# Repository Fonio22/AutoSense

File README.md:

# AutoSense

AutoSense is an Edge-IoT vehicle monitoring project based on an ESP32-S3 OBD-II/CAN adapter, a React Native mobile app, Firebase services, and a LaTeX thesis document.

Repository: <https://github.com/Fonio22/AutoSense>

## What It Does

- Reads vehicle telemetry from OBD-II over CAN.
- Stores compact binary history locally on the ESP32-S3.
- Streams live telemetry to the mobile app through BLE.
- Exports unsynced binary logs from the ESP32-S3 to the app without deleting them from flash.
- Uploads historical log files to Firebase Storage and stores sync metadata in Firestore.
- Uses lightweight edge analysis with statistical baselines, Z-score, and Tiny Isolation Forest.
- Documents the project in the thesis under `Writting/main.tex`.

## Repository Layout

```text
OBD2-Firmware/       ESP32-S3 firmware, OBD-II service, BLE protocol, logger, anomaly analysis
app/                 Expo / React Native mobile app and Firebase rules
vehicle-profiles/    Vehicle profile definitions, including vw_passat_2016
kiCad/               PCB design and schematic files
outputs/             Processed datasets and exported analysis inputs
Writting/            LaTeX thesis source, figures, references, and compiled PDF
```

## Firmware

```bash
cd OBD2-Firmware
pio run
```

Main modules:

- `src/app.cpp`: boot sequence and main loop.
- `src/obd_service.cpp`: PID discovery, polling, and OBD-II decoding.
- `src/obd_binary_logger.*`: compact binary log storage and export.
- `src/obd_ble_protocol.*`: BLE commands, telemetry stream, and log sync.
- `src/anomaly_detector.*`: baseline, Z-score, Tiny Isolation Forest, and severity levels.

## Mobile App

```bash
cd app
npm install
npx tsc --noEmit
npm run lint
npm run ios
```

The app uses Expo Router, Firebase Auth, Firestore, Firebase Storage, SecureStore, BLE, and local file storage for downloaded OBD logs.

Profile resolver tests:

```bash
cd app
node --test functions/test/profile-resolver.test.mjs
```

## Thesis

```bash
cd Writting
latexmk -pdf -interaction=nonstopmode -file-line-error main.tex
```

Main files:

- `Writting/main.tex`: thesis source.
- `Writting/main.pdf`: generated thesis PDF.
- `Writting/Reference/references.bib`: bibliography.
- `Writting/Figures/`: diagrams, screenshots, test photos, and result charts.

## Validation Snapshot

The current thesis documents:

- Volkswagen Passat 2016 as the main real-vehicle validation profile.
- OBD-II simulator testing with a generic profile.
- A 60-day route-classified dataset with city, highway, and unknown segments.
- Functional tests for acquisition, BLE/USB communication, storage, visualization, and analysis.

## Safety Scope

AutoSense is designed as a read-only monitoring system. It does not erase diagnostic trouble codes, does not write to vehicle ECUs, and does not replace professional mechanical diagnosis.

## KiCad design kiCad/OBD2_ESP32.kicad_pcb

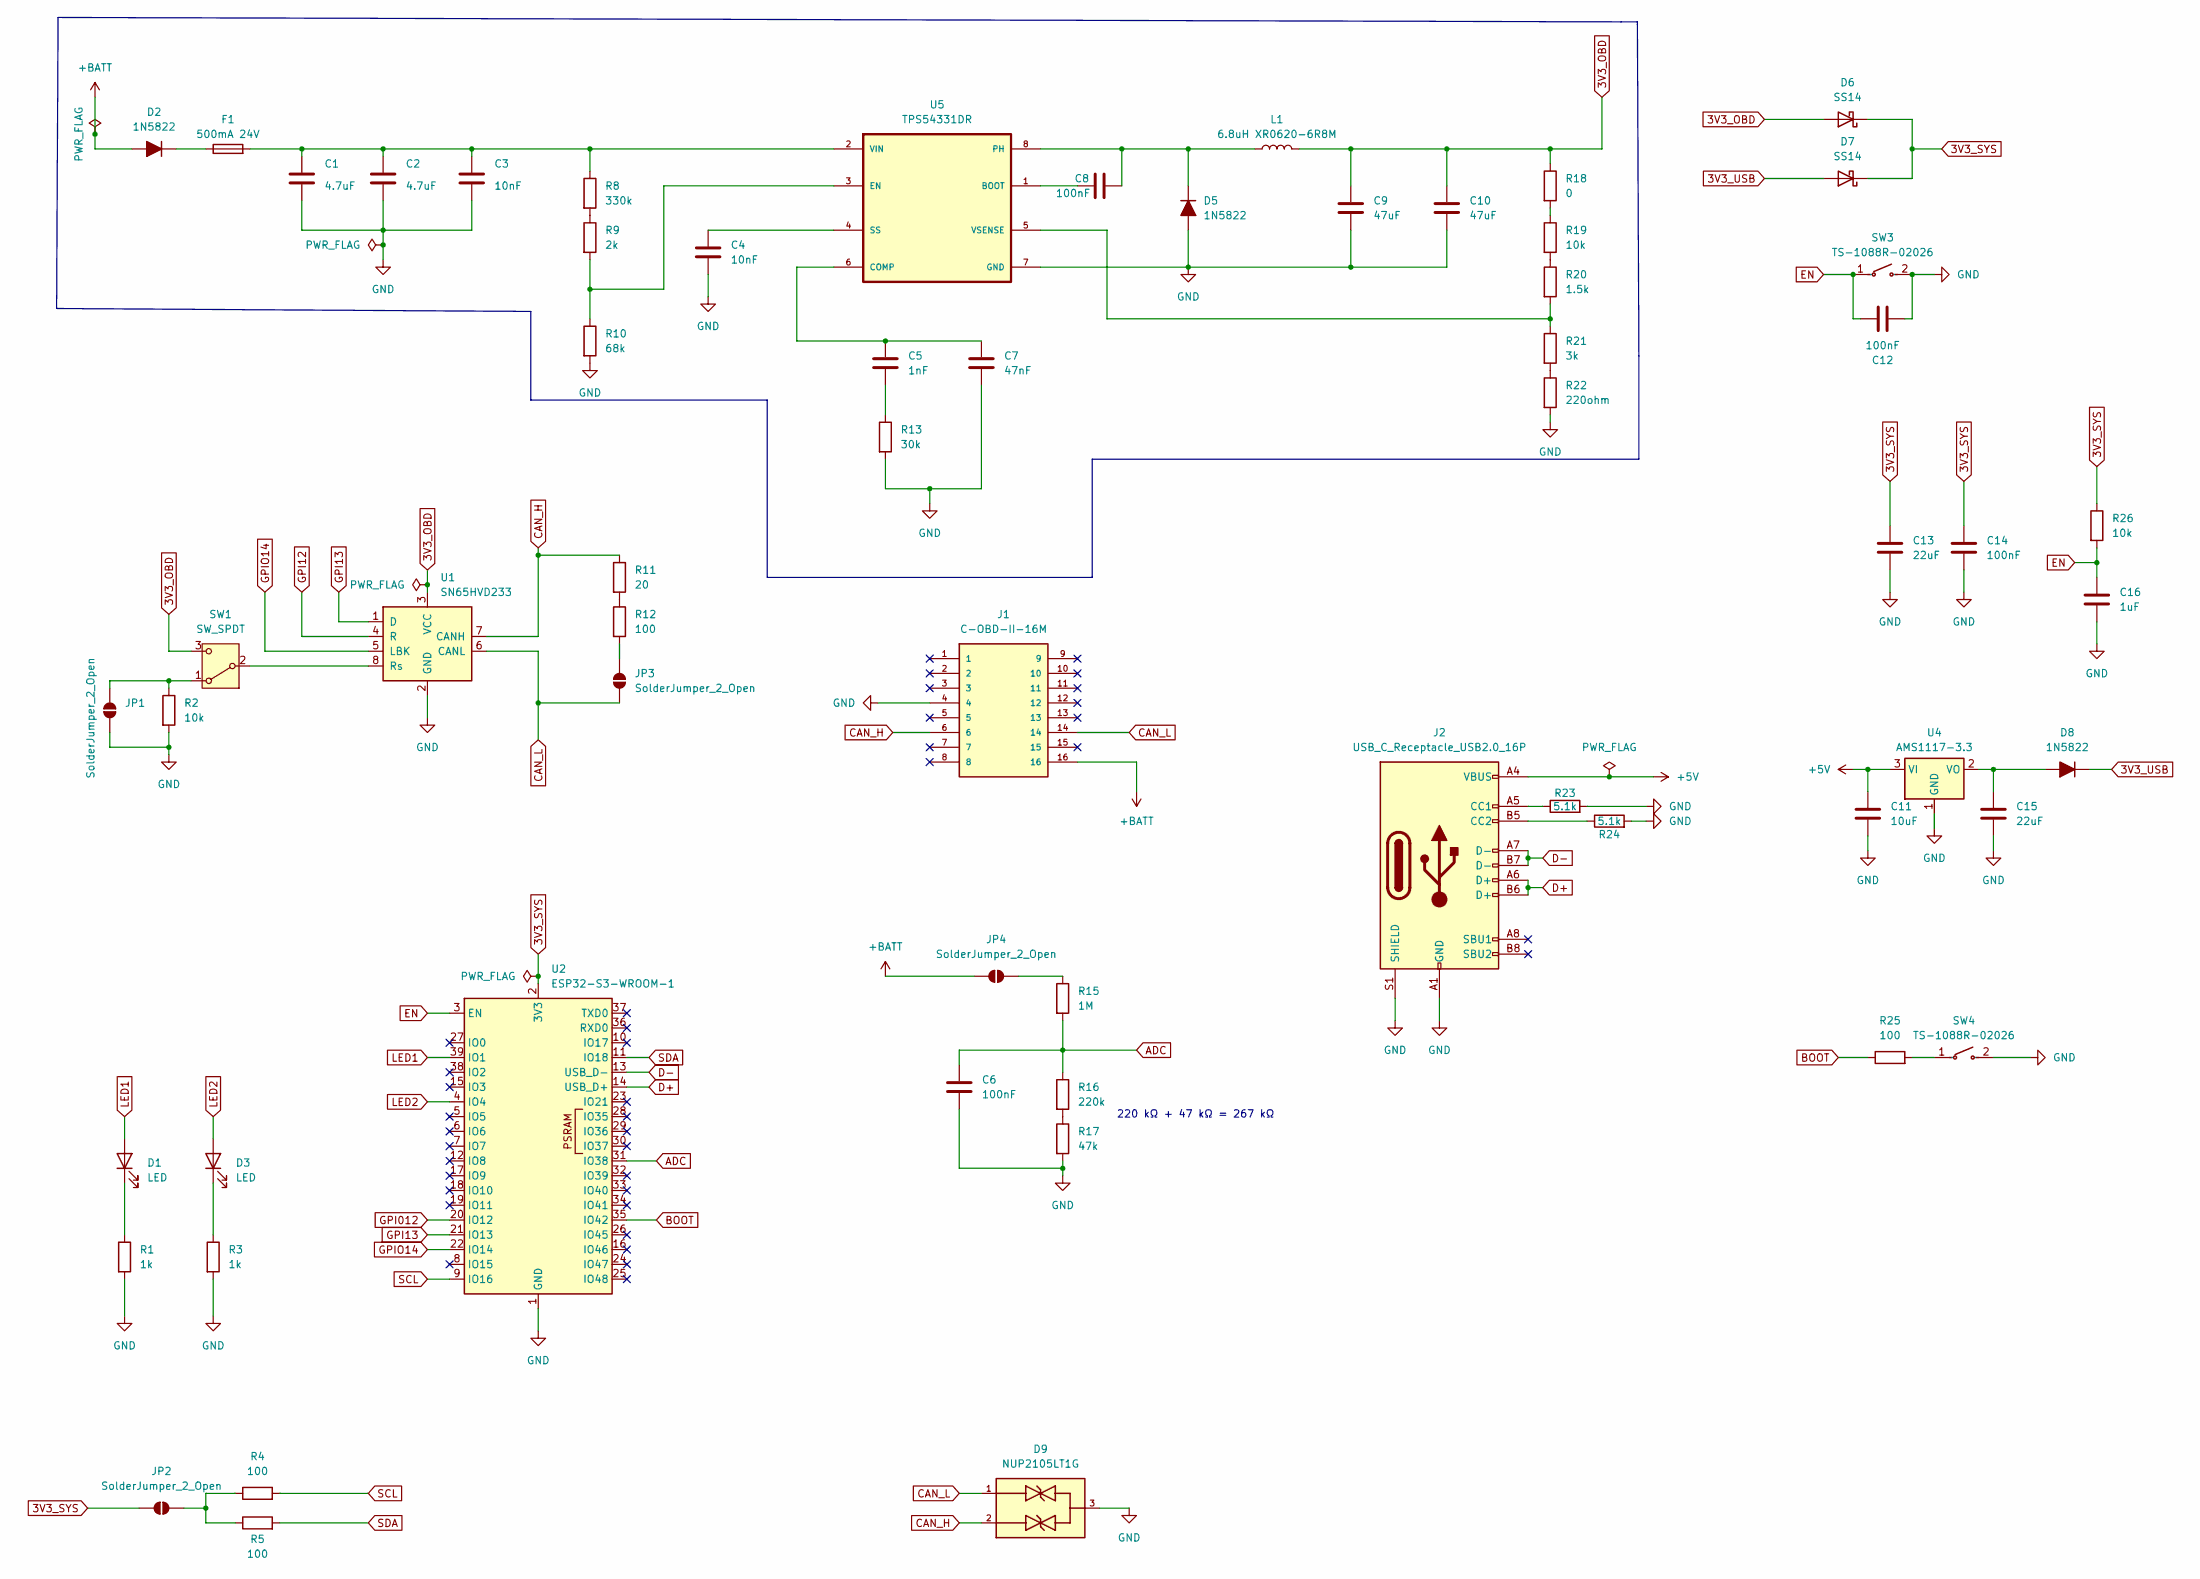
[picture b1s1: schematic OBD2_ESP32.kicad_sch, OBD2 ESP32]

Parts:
C1, C2: 4.7uF; C_0805_2012Metric_Pad1.18x1.45mm_HandSolder
C3, C4: 10nF; C_0805_2012Metric_Pad1.18x1.45mm_HandSolder
C5: 1nF; C_0805_2012Metric_Pad1.18x1.45mm_HandSolder
C6, C8, C12, C14: 100nF; C_0805_2012Metric_Pad1.18x1.45mm_HandSolder
C7: 47nF; C_0805_2012Metric_Pad1.18x1.45mm_HandSolder
C9, C10: 47uF; CP_EIA-7343-31_Kemet-D_HandSolder
C11: 10uF; C_0805_2012Metric_Pad1.18x1.45mm_HandSolder
C13, C15: 22uF; C_0805_2012Metric_Pad1.18x1.45mm_HandSolder
C16: 1uF; C_0805_2012Metric_Pad1.18x1.45mm_HandSolder
D1, D3: LED; LED_0805_2012Metric_Pad1.15x1.40mm_HandSolder
D2, D5, D8: 1N5822; D_SMA_Handsoldering
D6, D7: SS14; D_SMA
D9: NUP2105LT1G; SOT95P237X111-3N; PARTREV 10
F1: 500mA 24V; Fuse_1206_3216Metric_Pad1.42x1.75mm_HandSolder
J1: C-OBD-II-16M; COMTECH_C-OBD-II-16M; PARTREV A
J2: USB_C_Receptacle_USB2.0_16P; USB_C_Receptacle_GCT_USB4110
JP1, JP2, JP3, JP4: SolderJumper_2_Open; SolderJumper-2_P1.3mm_Open_Pad1.0x1.5mm
L1: 6.8uH XR0620-6R8M; L_APV_APH0620
R1, R3: 1k; R_0805_2012Metric_Pad1.20x1.40mm_HandSolder
R2, R19, R26: 10k; R_0805_2012Metric_Pad1.20x1.40mm_HandSolder
R4, R5, R12, R25: 100; R_0805_2012Metric_Pad1.20x1.40mm_HandSolder
R8: 330k; R_0805_2012Metric_Pad1.20x1.40mm_HandSolder
R9: 2k; R_0805_2012Metric_Pad1.20x1.40mm_HandSolder
R10: 68k; R_0805_2012Metric_Pad1.20x1.40mm_HandSolder
R11: 20; R_0805_2012Metric_Pad1.20x1.40mm_HandSolder
R13: 30k; R_0805_2012Metric_Pad1.20x1.40mm_HandSolder
R15: 1M; R_0805_2012Metric_Pad1.20x1.40mm_HandSolder
R16: 220k; R_0805_2012Metric_Pad1.20x1.40mm_HandSolder
R17: 47k; R_0805_2012Metric_Pad1.20x1.40mm_HandSolder
R18: 0; R_0805_2012Metric_Pad1.20x1.40mm_HandSolder
R20: 1.5k; R_0805_2012Metric_Pad1.20x1.40mm_HandSolder
R21: 3k; R_0805_2012Metric_Pad1.20x1.40mm_HandSolder
R22: 220ohm; R_0805_2012Metric_Pad1.20x1.40mm_HandSolder
R23, R24: 5.1k; R_0805_2012Metric_Pad1.20x1.40mm_HandSolder
SW1: SW_SPDT; SW_SPDT_Shouhan_MSK12C02
SW3, SW4: TS-1088R-02026; BUTTON TS-1088R-02026; Manufacturer Part TS-1088R-02026
U1: SN65HVD233; SOIC-8_3.9x4.9mm_P1.27mm
U2: ESP32-S3-WROOM-1
U4: AMS1117-3.3; SOT-223-3_TabPin2
U5: TPS54331DR; SOIC127P599X175-8N

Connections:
3V3_OBD: C9.1, C10.1, D6.2 (A), L1.2, R18.1, SW1.3 (C), U1.3 (VCC)
3V3_SYS: C13.1, C14.1, D6.1 (K), D7.1 (K), JP2.2 (B), R26.1, U2.2 (3V3)
3V3_USB: D7.2 (A), D8.1 (K)
+5V: C11.1, J2.A4 (VBUS), J2.A9 (VBUS), J2.B4 (VBUS), J2.B9 (VBUS), U4.3 (VI)
+BATT: D2.2 (A), J1.16, JP4.2 (B)
ADC: C6.1, R15.2, R16.1, U2.31 (IO38)
BOOT: R25.1, U2.35 (IO42)
CAN_H: D9.2, J1.6, R11.1, U1.7 (CANH)
CAN_L: D9.1, J1.14, JP3.1 (A), U1.6 (CANL)
D+: J2.A6 (D+), J2.B6 (D+), U2.14 (USB_D+)
D-: J2.A7 (D-), J2.B7 (D-), U2.13 (USB_D-)
EN: C12.1, C16.1, R26.2, SW3.1, U2.3 (EN)
GND: C1.2, C2.2, C3.2, C4.2, C6.2, C7.2, C9.2, C10.2, C11.2, C12.2, C13.2, C14.2, C15.2, C16.2, D5.2 (A), D9.3, J1.4, J2.A1 (GND), J2.A12 (GND), J2.B1 (GND), J2.B12 (GND), J2.S1 (SHIELD), JP1.1 (A), R1.2, R2.2, R3.2, R10.2, R13.2, R17.2, R22.2, R23.2, R24.2, SW3.2, SW4.2, U1.2 (GND), U2.1 (GND), U2.40 (GND), U2.41 (GND), U4.1 (GND), U5.7 (GND)
GPI05: U1.1 (D), U2.21 (IO13)
GPIO22: U1.5 (LBK), U2.22 (IO14)
LED1: D1.2 (A), U2.39 (IO1)
LED2: D3.2 (A), U2.4 (IO4)
unnamed: C5.2, R13.1
unnamed: D1.1 (K), R1.1
unnamed: D2.1 (K), F1.1
unnamed: D3.1 (K), R3.1
unnamed: C8.2, D5.1 (K), L1.1, U5.8 (PH)
unnamed: C15.1, D8.2 (A), U4.2 (VO)
unnamed: J2.A5 (CC1), R23.1
unnamed: J2.B5 (CC2), R24.1
unnamed: JP1.2 (B), R2.1, SW1.1 (A)
unnamed: JP2.1 (A), R4.1, R5.1
unnamed: JP3.2 (B), R12.2
unnamed: JP4.1 (A), R15.1
unnamed: R8.2, R9.1
unnamed: R11.2, R12.1
unnamed: R16.2, R17.1
unnamed: R18.2, R19.1
unnamed: R19.2, R20.1
unnamed: R21.2, R22.1
unnamed: R25.2, SW4.1
unnamed: SW1.2 (B), U1.8 (Rs)
unnamed: C8.1, U5.1 (BOOT)
unnamed: C5.1, C7.1, U5.6 (COMP)
unnamed: R9.2, R10.1, U5.3 (EN)
unnamed: C4.1, U5.4 (SS)
unnamed: C1.1, C2.1, C3.1, F1.2, R8.1, U5.2 (VIN)
unnamed: R20.2, R21.1, U5.5 (VSENSE)
SCL: R4.2, U2.9 (IO16)
SDA: R5.2, U2.11 (IO18)

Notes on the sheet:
220 kΩ + 47 kΩ = 267 kΩ

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
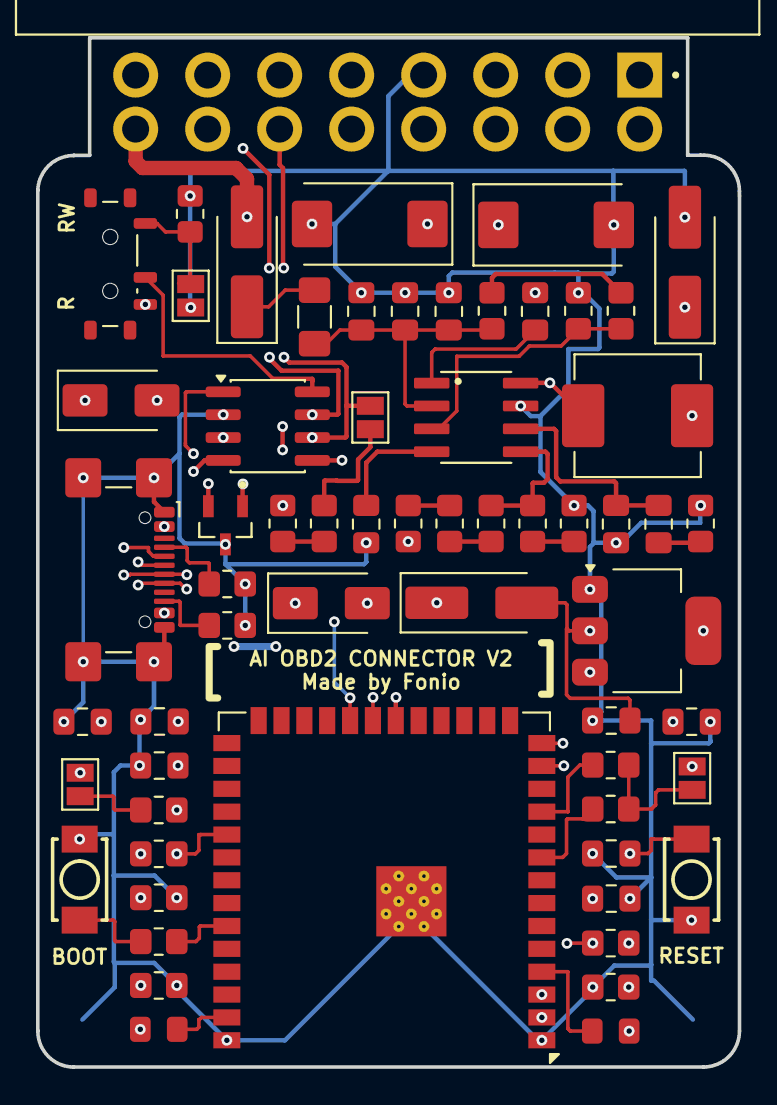
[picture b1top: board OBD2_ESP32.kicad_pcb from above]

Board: 4 copper layers, 39.0 x 57.2 mm, 62 parts (0 on the bottom side), 46 nets.

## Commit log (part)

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2026-06-14 Refactor code structure for improved readability and maintainability
2026-06-15 Update README and configuration for USB-CDC dashboard; remove UDP references
2026-06-15 Add UDS VAG Scanner and supporting tools
    - Implemented UdsVagScanner class for handling UDS communication with VAG modules.
    - Added audit_read_only_policy.py to enforce read-only policy for OBD and UDS services.
    - Introduced capture_obd_report.py for capturing and processing OBD reports from the serial dashboard.
    - Defined constants for safe and blocked OBD/UDS services.
    - Implemented functions for parsing and validating service requests and responses.
    - Added CSV output functionality for captured metrics and VAG module data.
2026-06-20 feat: add session provider and user data management
    - Implemented SessionProvider to manage user authentication state and profile data.
    - Created autosense-data module for user and trip data structures, including default values and utility functions.
    - Introduced firebase-client for Firebase initialization and secure storage handling.
    - Developed trip-tracking module for managing trip sessions, location updates, and trip document creation.
    - Added storage rules for user avatar uploads to Firebase Storage, ensuring proper authentication and file size/type validation.
2026-06-21 feat(obd): add vehicle profile management and telemetry hooks
    - Implemented profile caching in `profile-cache.ts` for saving and loading active vehicle profiles.
    - Created `useObdTelemetry` hook in `use-obd-telemetry.ts` for managing OBD telemetry data with demo mode support.
    - Defined vehicle profile structure and validation logic in `vehicle-profile.ts`, including SHA-256 hashing for integrity checks.
    - Added vehicle profiles for generic OBD2, OBD2 simulator, and VW Passat 2016, with metadata for easy access.
    - Documented vehicle profile usage and safety rules in `README.md`.
2026-06-27 refactor: remove trips layout and screen components; implement new trip detail and index screens
    - Deleted the old trips layout and index files.
    - Added a new trip detail screen with enhanced UI and functionality.
    - Introduced a new trips index screen to display trip statistics and list.
    - Updated app-tabs to remove the trips tab and adjust navigation logic.
